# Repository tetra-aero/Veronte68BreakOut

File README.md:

# Veronte68BreakOut
Embention Veronte Autopilot 1x, 68 pin to 2.54 pitch adapter board

## Veronte68 pinout

- detail pinout
    - Hardware Installation
https://manuals.embention.com/1x/en/4.5/hardware%20installation/index.html#veronte-autopilot-1x-i-o-signals

- more information (internal): 
    - Log, make Veronte 68 pin to 2.54 pitch adapter board
https://www.notion.so/tetraaviation/Log-make-Veronte-68-pin-to-2-54-pitch-adapter-board-f0575a66330b4e21ac6df0196d4a23b4

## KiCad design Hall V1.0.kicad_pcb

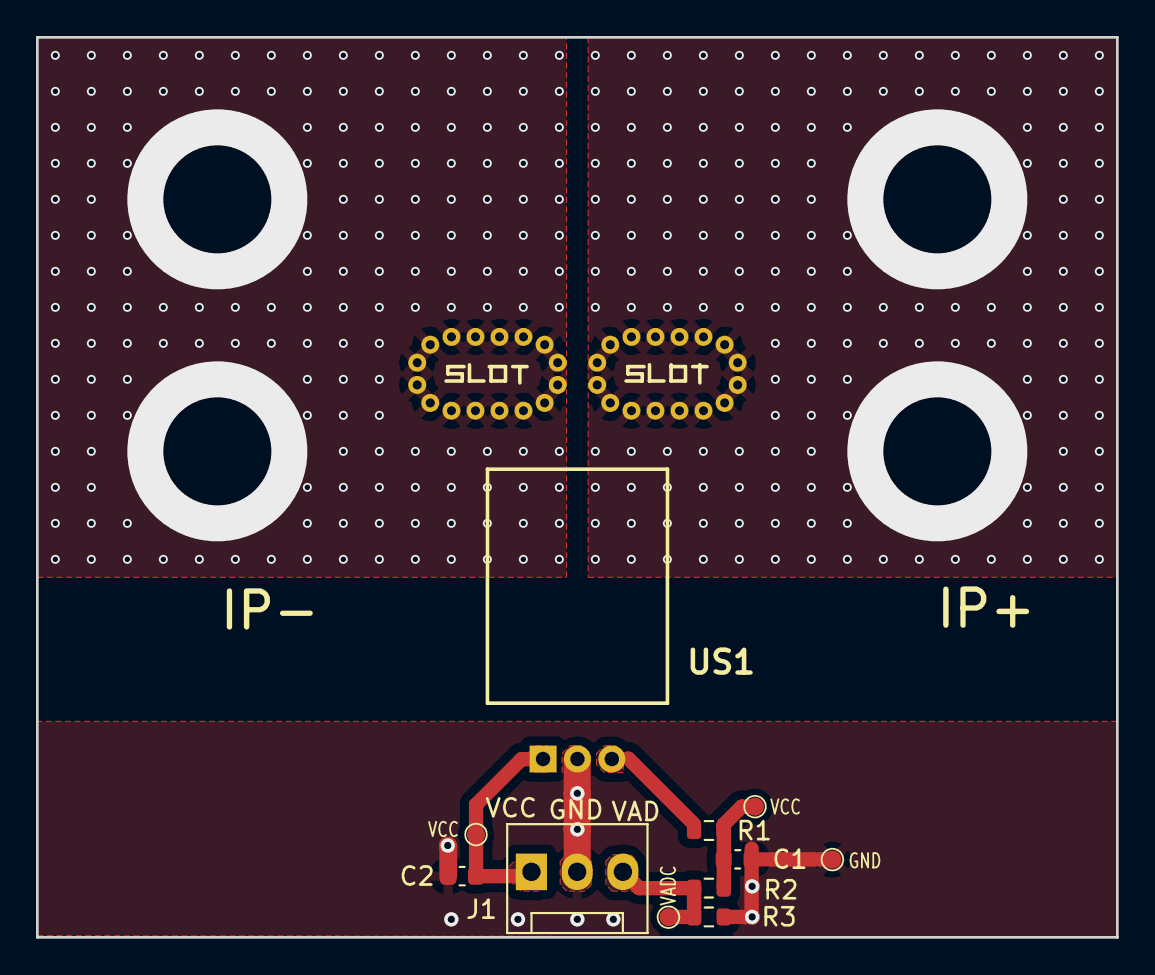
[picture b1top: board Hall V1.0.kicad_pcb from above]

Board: 2 copper layers, 60.0 x 50.0 mm, 11 parts (0 on the bottom side), 7 nets.

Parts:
C1: CF; C_0603_1608Metric
C2: 0.1uF; C_0603_1608Metric
GND: TestPoint; P001
J1: Conn_01x03_Pin; FanPinHeader_1x03_P2.54mm_Vertical
R1: RF; R_0603_1608Metric
R2: 300K; R_0603_1608Metric
R3: 100K; R_0603_1608Metric
US1: ACS772ECB-200B-PFF-T; ACS772ECB200BPFFT
VADC: TestPoint; P001
VCC: TestPoint; P001
VCC#2: TestPoint; P001

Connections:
/IP+: US1.4 (IP+_1), US1.21 (IP+_2), US1.22 (IP+_3), US1.23 (IP+_4), US1.24 (IP+_5), US1.25 (IP+_6), US1.26 (IP+_7), US1.27 (IP+_8), US1.28 (IP+_9), US1.29 (IP+_10), US1.30 (IP+_11), US1.31 (IP+_12), US1.32 (IP+_13), US1.33 (IP+_14), US1.34 (IP+_15), US1.35 (IP+_16)
/IP-: US1.5 (IP-_1), US1.6 (IP-_2), US1.7 (IP-_3), US1.8 (IP-_4), US1.9 (IP-_5), US1.10 (IP-_6), US1.11 (IP-_7), US1.12 (IP-_8), US1.13 (IP-_9), US1.14 (IP-_10), US1.15 (IP-_11), US1.16 (IP-_12), US1.17 (IP-_13), US1.18 (IP-_14), US1.19 (IP-_15), US1.20 (IP-_16)
/VADC: J1.3, R2.2, R3.1, VADC.1
/Vout: C1.1, R1.1, R2.1, VCC.1
GND1: C1.2, C2.1, GND.1, J1.2, R3.2, US1.2 (GND)
unnamed: R1.2, US1.3 (VIOUT)
VCC: C2.2, J1.1, US1.1 (VCC), VCC#2.1

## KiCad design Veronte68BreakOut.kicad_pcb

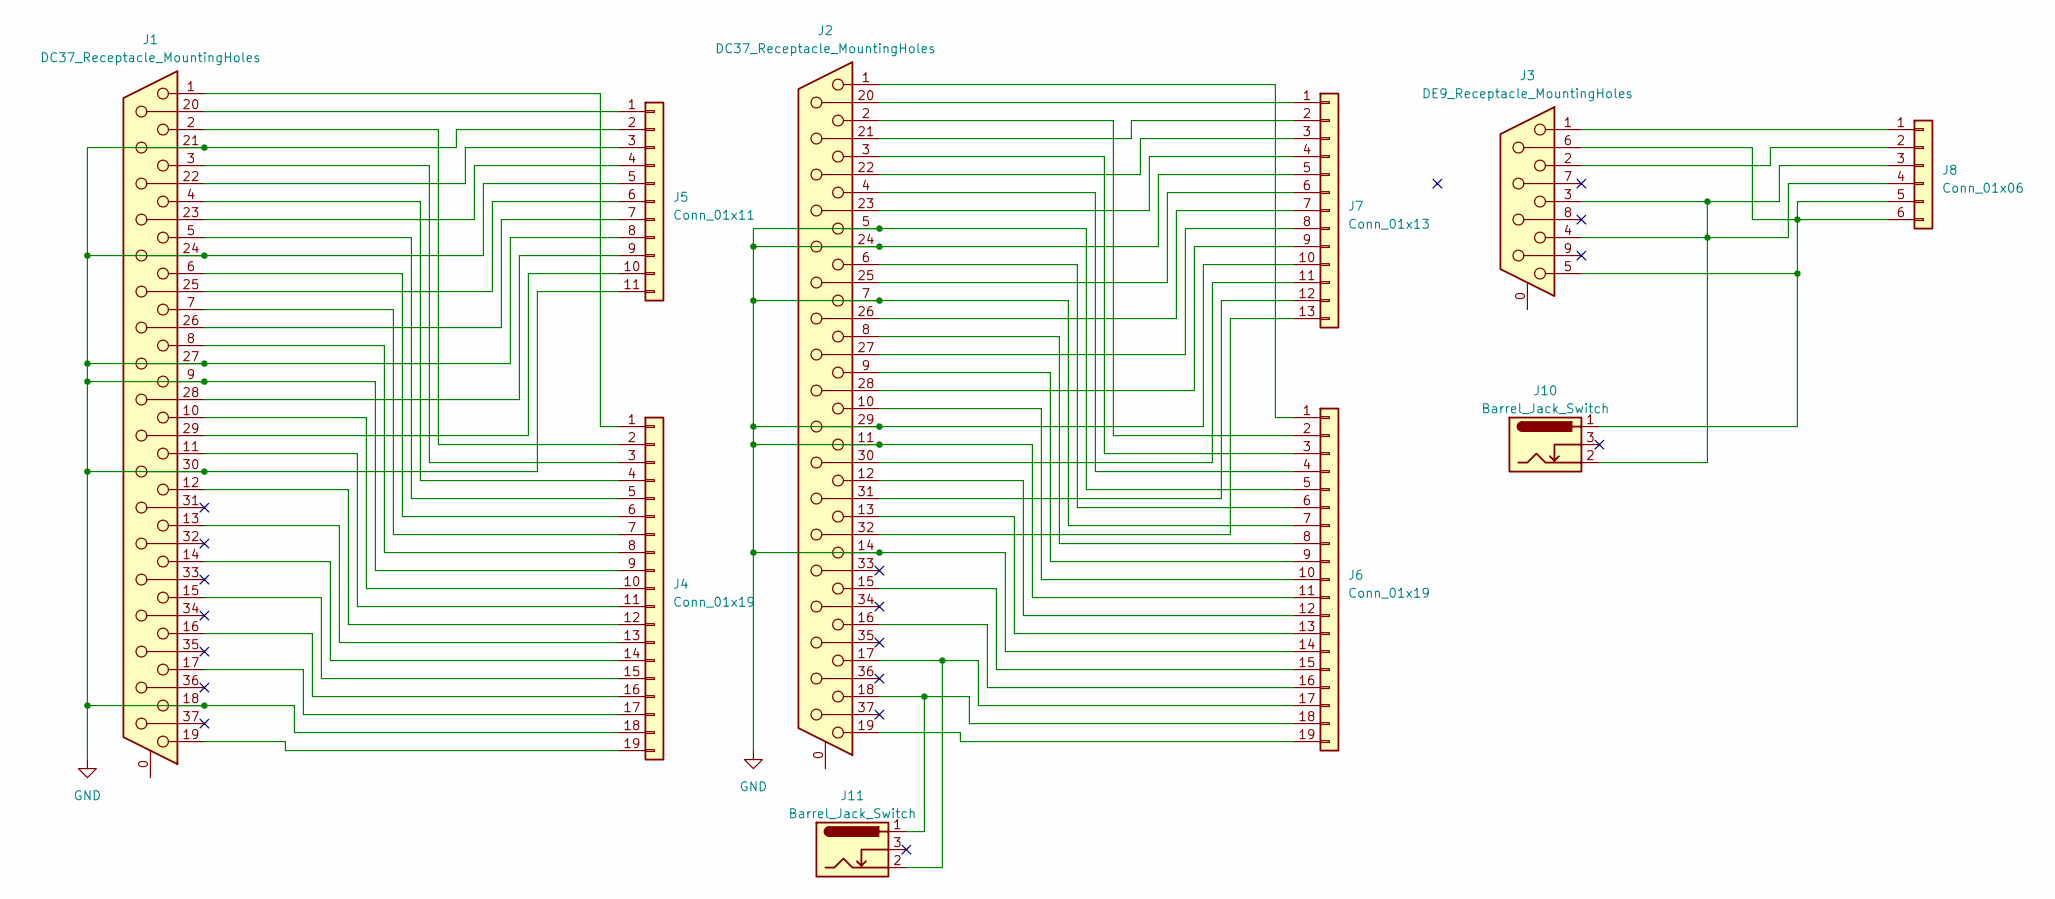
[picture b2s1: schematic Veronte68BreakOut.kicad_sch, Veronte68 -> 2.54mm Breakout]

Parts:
J1, J2: DC37_Receptacle_MountingHoles; DSUB-37_Female_Horizontal_P2.77x2.84mm_EdgePinOffset7.70mm_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
J3: DE9_Receptacle_MountingHoles; DSUB-9_Female_Horizontal_P2.77x2.84mm_EdgePinOffset4.94mm_H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
J4, J6: Conn_01x19; PinHeader_1x19_P2.54mm_Vertical
J5: Conn_01x11; PinHeader_1x11_P2.54mm_Vertical
J7: Conn_01x13; PinHeader_1x13_P2.54mm_Vertical
J8: Conn_01x06; PinHeader_1x06_P2.54mm_Vertical
J10, J11: Barrel_Jack_Switch; BarrelJack_GCT_DCJ200-10-A_Horizontal

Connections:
GND: J1.9, J1.18, J1.21, J1.24, J1.27, J1.30, J2.5, J2.7, J2.11, J2.14, J2.24, J2.29, J4.9, J4.18, J5.2, J5.5, J5.8, J5.11, J6.5, J6.7, J6.11, J6.14, J7.5, J7.10
unnamed: J1.1, J4.1
unnamed: J1.2, J4.2
unnamed: J1.3, J4.3
unnamed: J1.4, J4.4
unnamed: J1.5, J4.5
unnamed: J1.6, J4.6
unnamed: J1.7, J4.7
unnamed: J1.8, J4.8
unnamed: J1.10, J4.10
unnamed: J1.11, J4.11
unnamed: J1.12, J4.12
unnamed: J1.13, J4.13
unnamed: J1.14, J4.14
unnamed: J1.15, J4.15
unnamed: J1.16, J4.16
unnamed: J1.17, J4.17
unnamed: J1.19, J4.19
unnamed: J1.20, J5.1
unnamed: J1.22, J5.3
unnamed: J1.23, J5.4
unnamed: J1.25, J5.6
unnamed: J1.26, J5.7
unnamed: J1.28, J5.9
unnamed: J1.29, J5.10
unnamed: J2.1, J6.1
unnamed: J2.2, J6.2
unnamed: J2.3, J6.3
unnamed: J2.4, J6.4
unnamed: J2.6, J6.6
unnamed: J2.8, J6.8
unnamed: J2.9, J6.9
unnamed: J2.10, J6.10
unnamed: J2.12, J6.12
unnamed: J2.13, J6.13
unnamed: J2.15, J6.15
unnamed: J2.16, J6.16
unnamed: J2.17, J6.17, J11.2
unnamed: J2.18, J6.18, J11.1
unnamed: J2.19, J6.19
unnamed: J2.20, J7.1
unnamed: J2.21, J7.2
unnamed: J2.22, J7.3
unnamed: J2.23, J7.4
unnamed: J2.25, J7.6
unnamed: J2.26, J7.7
unnamed: J2.27, J7.8
unnamed: J2.28, J7.9
unnamed: J2.30, J7.11
unnamed: J2.31, J7.12
unnamed: J2.32, J7.13
unnamed: J3.1, J8.1
unnamed: J3.2, J8.2
unnamed: J3.3, J3.4, J8.3, J8.4, J10.2
unnamed: J3.5, J3.6, J8.5, J8.6, J10.1

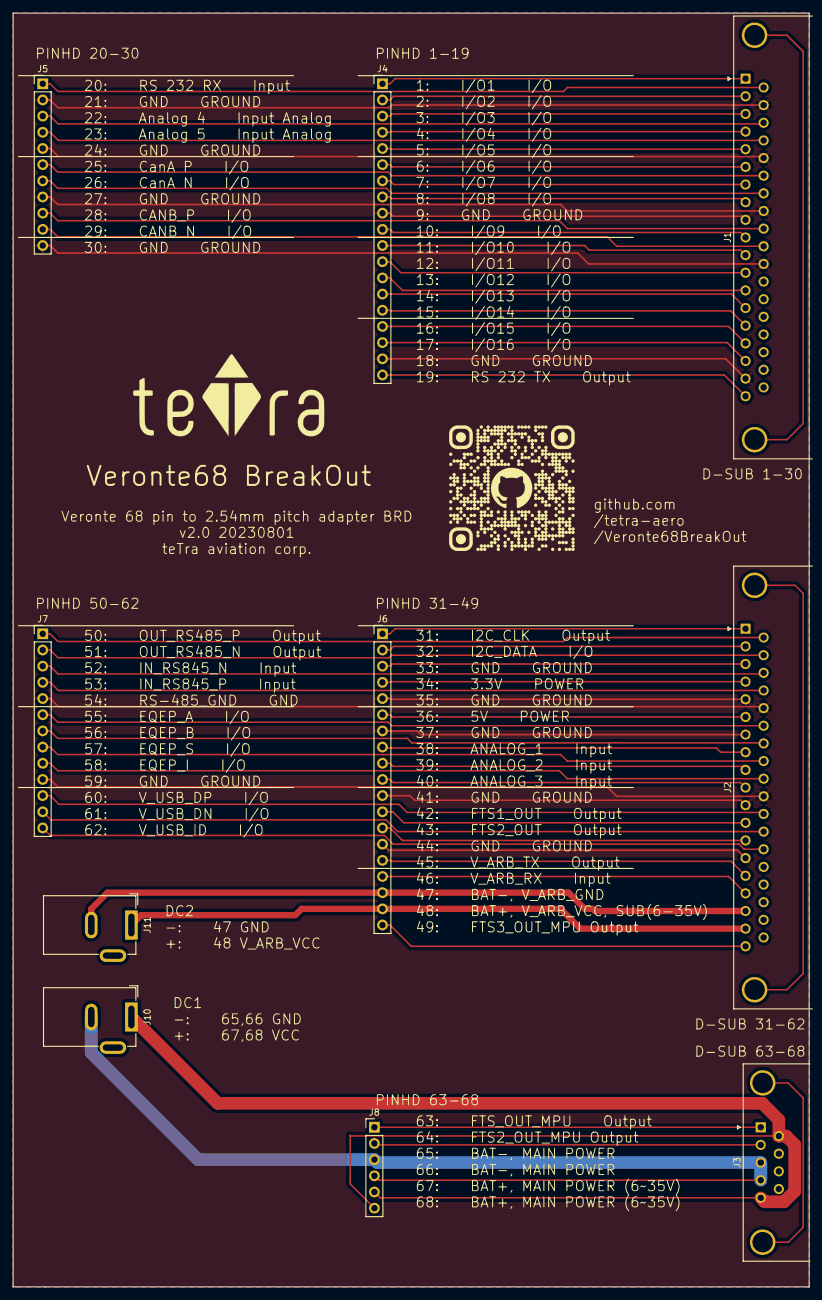
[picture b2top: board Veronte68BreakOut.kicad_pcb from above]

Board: 2 copper layers, 125.0 x 200.0 mm, 10 parts (0 on the bottom side), 55 nets.

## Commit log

2023-07-05 update gitignore
2023-07-05 add schematic
2023-07-06 pcbを作成
2023-07-06 rooting finish
2023-07-06 add silkscreen
2023-07-07 add v1.3
    - change 60/61/62 pin
    - change number of pin header
    - add GND and solid GND pattern
2023-07-07 order v1
    order v1
2023-07-27 Hall Sensor
2023-07-31 Add files via upload
    Add a voltage divider resistor for AD detection to enable the external 3.3V MCU to directly read the AD value.
2023-07-31 Add conductable hole for high current
    Add 4 conductable holes、Add test points、Adjust PCB board dimensions to 60mm50mm 、Increase the width of the IP pin traces to 30mm
2023-08-01 add v2.0
    add v2.0
2023-08-02 ACS772ECB-200B-PFF-T library footprint 3D model
2024-03-06 add other file
    add other file
2024-03-06 add readme
    add readme
2024-03-06 update readme
    update readme
2024-03-06 add license, GPL v3.0
    add license, GPL v3.0
